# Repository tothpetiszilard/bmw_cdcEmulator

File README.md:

BMW (E46 and E39) CDC (cd changer) emulator project

- Emulates a CD changer node on the IBUS network
- Controls and reads status of KRC 86B V4.0 bluetooth module (onboard)
- Controls a dfPlayer mini USB and microSD card music player module (onboard)
- Receives multifuction steering wheel commands
- Receives commands and status from the original radio
- Supports some configuration options which can be set using the original radio interface

HW design done in EAGLE
SW is done in MPLABX using its MCC code generator

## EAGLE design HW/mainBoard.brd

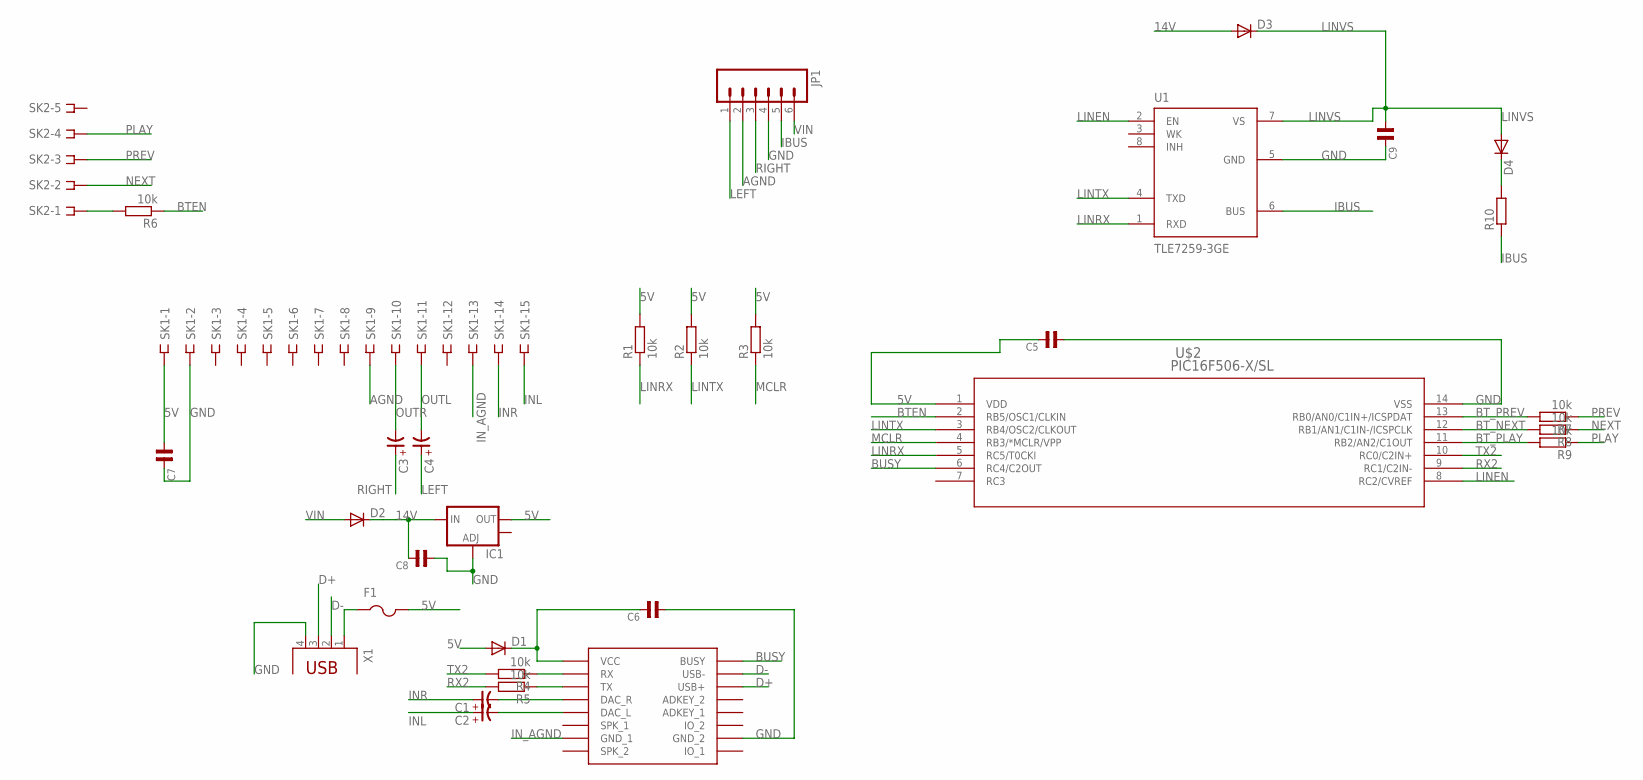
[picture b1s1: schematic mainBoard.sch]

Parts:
C1, C2, C3, C4: CP-3258-TE-B; 3528-TE-B
C5, C6, C7, C9: C0603; 0603
C8: C1206; 1206
D1, D2: DIODESMA-ALT; SMA-DIODE_ALT
D3, D4: DIODE-SOD80C; SOD80C
F1: PTCFUSE-1812; 1812
IC1: V_REG_LM1117SOT223; SOT223
JP1: M06LONGPADS; 1X06_LONGPADS
R1, R2, R3, R4, R5, R6, R7, R8, R9: 10k; R0603
R10: R-EU_R0603; R0603
SK1: DF3-15S; DF3S-15
SK2: DF3-05S; DF3S-05
U1: TLE7259-3GE; SOIC127P600X175-8N-3
U$1: DFPLAYER
U$2: PIC16F506-X/SL; SOIC14-N_MC
X1: PN87520

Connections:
5V: C5.2, C7.1, D1.A, F1.2, IC1.2 (OUT), R1.2, R2.2, R3.2, SK1.1, U$2.1 (VDD)
14V: C8.2, D2.C, D3.A, IC1.3 (IN)
AGND: JP1.2, SK1.9
BTEN: R6.1, U$2.2 (RB5/OSC1/CLKIN)
BT_NEXT: R8.2, U$2.12 (RB1/AN1/C1IN-/ICSPCLK)
BT_PLAY: R9.2, U$2.11 (RB2/AN2/C1OUT)
BT_PREV: R7.2, U$2.13 (RB0/AN0/C1IN+/ICSPDAT)
BUSY: U$1.BUSY, U$2.6 (RC4/C2OUT)
D+: U$1.USB+, X1.3
D-: U$1.USB-, X1.2
GND: C5.1, C6.1, C7.2, C8.1, C9.2, IC1.1 (ADJ), JP1.4, SK1.2, U1.5 (GND), U$1.GND_2, U$2.14 (VSS), X1.4
IBUS: JP1.5, R10.1, U1.6 (BUS)
INL: C2.+, SK1.15
INR: C1.+, SK1.14
IN_AGND: SK1.13, U$1.GND_1
LEFT: C4.+, JP1.1
LINEN: U1.2 (EN), U$2.8 (RC2/CVREF)
LINRX: R1.1, U1.1 (RXD), U$2.5 (RC5/T0CKI)
LINTX: R2.1, U1.4 (TXD), U$2.3 (RB4/OSC2/CLKOUT)
LINVS: C9.1, D3.C, D4.A, U1.7 (VS)
MCLR: R3.1, U$2.4 (RB3/*MCLR/VPP)
unnamed: C2.-, U$1.DAC_L
unnamed: C1.-, U$1.DAC_R
unnamed: C6.2, D1.C, U$1.VCC
unnamed: R4.1, U$1.RX
unnamed: R5.1, U$1.TX
unnamed: F1.1, X1.1
unnamed: D4.C, R10.2
unnamed: R6.2, SK2.1
NEXT: R8.1, SK2.2
OUTL: C4.-, SK1.11
OUTR: C3.-, SK1.10
PLAY: R9.1, SK2.4
PREV: R7.1, SK2.3
RIGHT: C3.+, JP1.3
RX2: R5.2, U$2.9 (RC1/C2IN-)
TX2: R4.2, U$2.10 (RC0/C2IN+)
VIN: D2.A, JP1.6

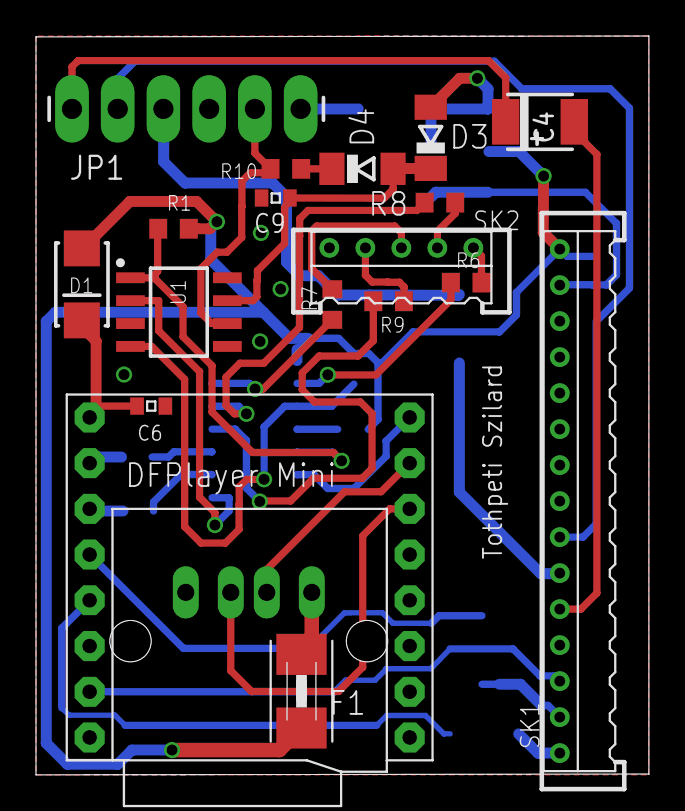
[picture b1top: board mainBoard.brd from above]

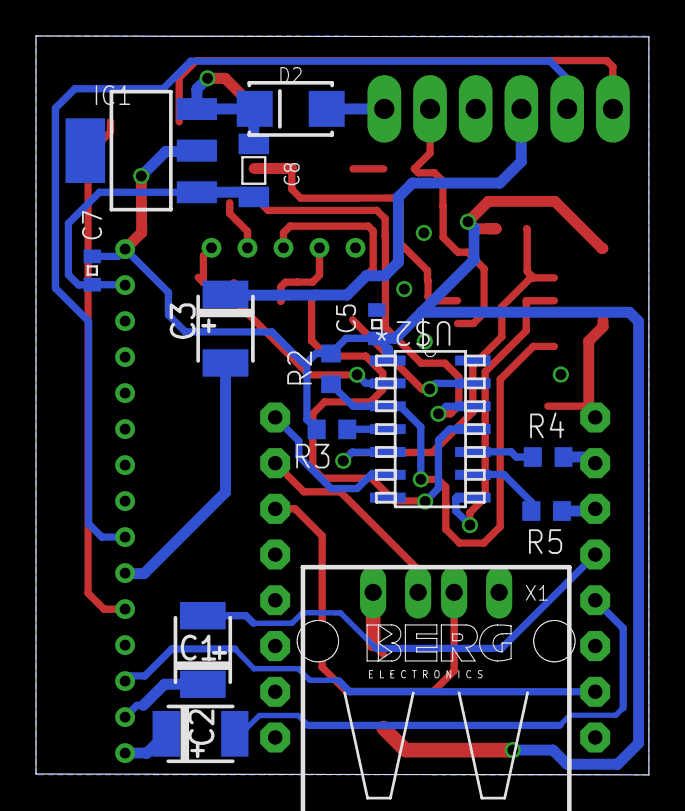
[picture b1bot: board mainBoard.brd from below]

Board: 2 copper layers, 34.0 x 41.0 mm, 32 parts (14 on the bottom side), 38 nets.

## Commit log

2022-10-21 Ignore bak (backup) files
2022-10-21 Added MPLABX project files
2022-10-21 Backup of an older version
2022-10-21 Add PC application src code (c#)

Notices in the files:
parts and their libraries:
SparkFun-DiscreteSemi: Licensing: Creative Commons ShareAlike 4.0 International - https://creativecommons.org/licenses/by-sa/4.0
